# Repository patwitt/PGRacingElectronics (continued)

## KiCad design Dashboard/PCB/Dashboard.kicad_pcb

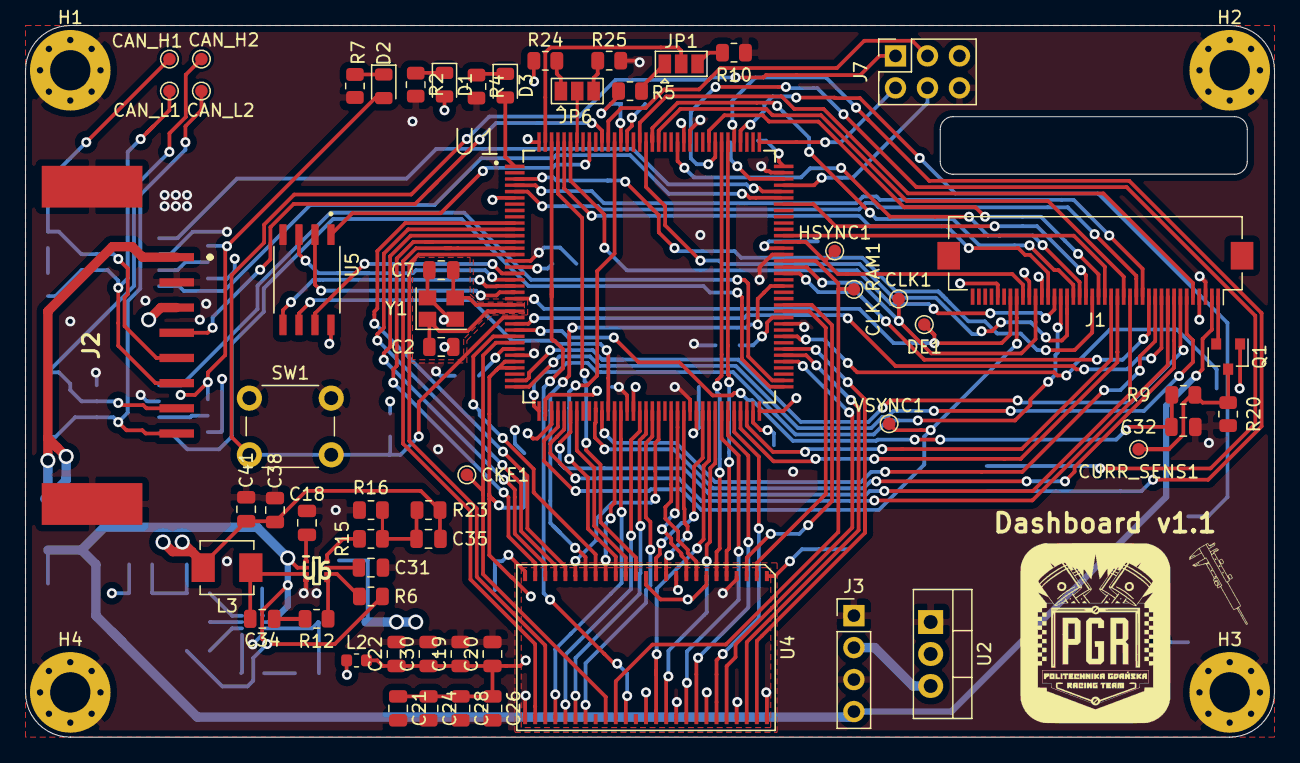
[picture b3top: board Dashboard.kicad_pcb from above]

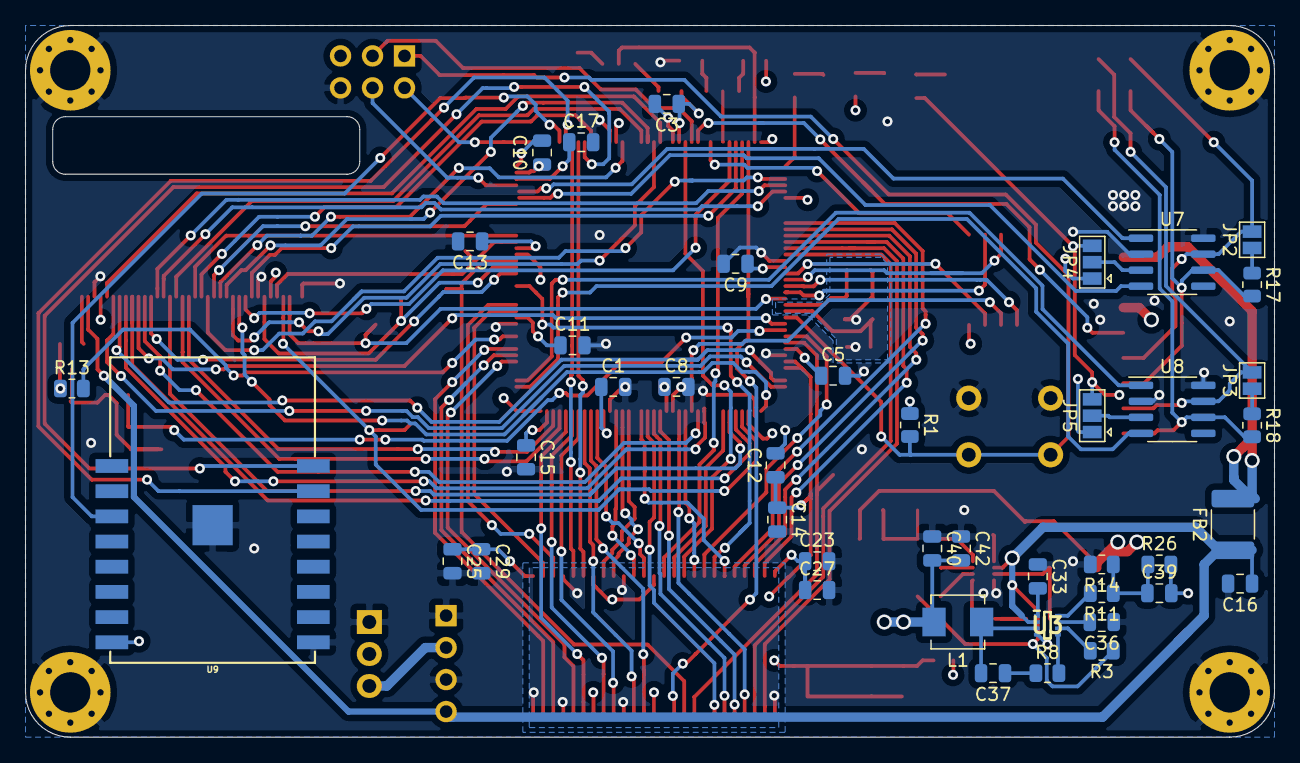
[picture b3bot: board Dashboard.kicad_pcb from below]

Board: 4 copper layers, 99.2 x 56.5 mm, 107 parts (42 on the bottom side), 131 nets.

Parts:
C1, C3, C5, C8, C9, C10, C11, C13, C16, C19, C20, C21, C22, C23, C24, C25, C26, C27, C28, C29, C30, C32: 100nF; C_0805_2012Metric
C2, C7: 14p; C_0805_2012Metric
C12, C18, C31, C33, C34, C36, C37: 1uF; C_0805_2012Metric
C14: 10nF; C_0805_2012Metric
C15, C17: 2.2uF; C_0805_2012Metric
C35, C39: 10pF; C_0805_2012Metric
C38, C40, C41, C42: 22uF; C_0805_2012Metric
CAN_H1, CAN_H2: TestPoint; TestPoint_Pad_D1.0mm
CAN_L1, CAN_L2: TestPoint; TestPoint_Pad_D1.0mm
CKE1: TestPoint; TestPoint_Pad_D1.0mm
CLK1: TestPoint; TestPoint_Pad_D1.0mm
CLK_RAM1: TestPoint; TestPoint_Pad_D1.0mm
CURR_SENS1: TestPoint; TestPoint_Pad_D1.0mm
D1: LED_3.3V; LED_0805_2012Metric
D2, D3: LED_5V; LED_0805_2012Metric
DE1: TestPoint; TestPoint_Pad_D1.0mm
FB2: Ferrite_Bead; C_1812_4532Metric
H1, H2, H3, H4: MountingHole_Pad; MountingHole_3.2mm_M3_Pad_Via
HSYNC1: TestPoint; TestPoint_Pad_D1.0mm
J1: Display; Hirose_FH12-40S-0.5SH_1x40-1MP_P0.50mm_Horizontal
J2: 34912-6080; 349126080
J3: Conn_01x04_Female; PinHeader_1x04_P2.54mm_Vertical
J7: PROGRAMMER; PinSocket_2x03_P2.54mm_Vertical
JP1: PDR_ON; SolderJumper-3_P1.3mm_Open_Pad1.0x1.5mm
JP2: CAN1_RESISTOR; SolderJumper-2_P1.3mm_Open_Pad1.0x1.5mm
JP3: CAN2_RESISTOR; SolderJumper-2_P1.3mm_Open_Pad1.0x1.5mm
JP4, JP5: Jumper_3_Bridged12; SolderJumper-3_P1.3mm_Open_Pad1.0x1.5mm
JP6: BOOT0; SolderJumper-3_P1.3mm_Open_Pad1.0x1.5mm
L1: 3.3uH; L_Vishay_IHLP-1616
L2: 39nH; L_0603_1608Metric
L3: 2.2uH; L_Vishay_IHLP-1616
Q1: Q_NMOS_GDS; SOT-23
R1, R5, R10, R24, R25: 10k; R_0805_2012Metric
R2, R4, R7, R8, R9, R12, R13: R; R_0805_2012Metric
R3, R6: 100k; R_0805_2012Metric
R11, R15: 20k; R_0805_2012Metric
R14, R16: 13k; R_0805_2012Metric
R17, R18: 120; R_0805_2012Metric
R20: 1R; R_0805_2012Metric
R23, R26: 40.2k; R_0805_2012Metric
SW1: SW_SPST; SW_PUSH_6mm_H8mm
U1: STM32F767ZIT6; QFP50P2200X2200X160-144N
U2: IFX27001TFV33; TO-220-3_Vertical
U3, U6: MP2332H; SOTFL50P160X60-8N
U4: AS4C1M16S-6TCN; TSOP-II-50
U5: AT25SF128A-SHB-T; SOIC127P790X216-8N
U7, U8: MCP2561-E-SN; SOIC-8_3.9x4.9mm_P1.27mm
U9: ESP-12S
VSYNC1: TestPoint; TestPoint_Pad_D1.0mm
Y1: Crystal_GND24; Crystal_SMD_3225-4Pin_3.2x2.5mm

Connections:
+3.3VA: C12.1, C14.1, C19.1, C20.1, C21.1, C22.1, C24.1, C26.1, C28.1, C30.1, L2.2, U1.32, U1.33, U4.7, U4.13, U4.38, U4.44
+3V3: C1.1, C3.1, C5.1, C8.1, C9.1, C10.1, C11.1, C13.1, C23.1, C25.1, C27.1, C29.1, C39.2, C40.2, C42.2, D1.2, J1.4, J1.31, JP4.1, JP5.1, L1.2, L2.1, R1.1, R5.1, R24.1, R26.2, U1.6, U1.17, U1.30, U1.39, U1.52, U1.62, U1.72, U1.84, U1.95, U1.108, U1.121, U1.131, U1.144, U2.2, U4.1, U4.25, U5.8, U9.8
+5V: C35.2, C38.2, C41.2, D2.2, J2.3, J3.2, JP4.3, JP5.3, L3.2, R23.2, U2.3
+12L: C16.1, FB2.1, J1.2, J3.4, R3.1, R6.1, U3.2, U6.2
+12V: FB2.2, J2.1
/FMC_A0: U1.10, U4.21
/FMC_A1: U1.11, U4.22
/FMC_A2: U1.12, U4.23
/FMC_A3: U1.13, U4.24
/FMC_A4: U1.14, U4.27
/FMC_A5: U1.15, U4.28
/FMC_A6: U1.50, U4.29
/FMC_A7: U1.53, U4.30
/FMC_A8: U1.54, U4.31
/FMC_A9: U1.55, U4.32
/FMC_A10: U1.56, U4.20
/FMC_BA0: U1.89, U4.19
/FMC_D0: U1.85, U4.2
/FMC_D1: U1.86, U4.3
/FMC_D2: U1.114, U4.5
/FMC_D3: U1.115, U4.6
/FMC_D4: U1.58, U4.8
/FMC_D5: U1.59, U4.9
/FMC_D6: U1.60, U4.11
/FMC_D7: U1.63, U4.12
/FMC_D8: U1.64, U4.39
/FMC_D9: U1.65, U4.40
/FMC_D10: U1.66, U4.42
/FMC_D11: U1.67, U4.43
/FMC_D12: U1.68, U4.45
/FMC_D13: U1.77, U4.46
/FMC_D14: U1.78, U4.48
/FMC_D15: U1.79, U4.49
/FMC_NBL0: U1.141, U4.14
/FMC_NBL1: U1.142, U4.36
/FMC_SDCAS: U1.132, U4.16
/FMC_SDCKE0: CKE1.1, U1.29, U4.34
/FMC_SDCLK: CLK_RAM1.1, U1.93, U4.35
/FMC_SDNE0: U1.28, U4.18
/FMC_SDNRAS: U1.49, U4.17
/FMC_SDNWE: U1.43, U4.15
/LTDC_B0: J1.21, U1.3
/LTDC_B1: J1.22, U1.102
/LTDC_B2: J1.23, U1.122
/LTDC_B3: J1.24, U1.126
/LTDC_B4: J1.25, U1.127
/LTDC_B5: J1.26, U1.37
/LTDC_B6: J1.27, U1.139
/LTDC_B7: J1.28, U1.140
/LTDC_CLK: CLK1.1, J1.30, U1.92
/LTDC_DE: DE1.1, J1.34, U1.22
/LTDC_G0: J1.13, U1.4
/LTDC_G1: J1.14, U1.5
/LTDC_G2: J1.15, U1.42
/LTDC_G3: J1.16, U1.125
/LTDC_G4: J1.17, U1.69
/LTDC_G5: J1.18, U1.70
/LTDC_G6: J1.19, U1.97
/LTDC_G7: J1.20, U1.117
/LTDC_HSYNC: HSYNC1.1, J1.32, U1.96
/LTDC_R0: J1.5, U1.128
/LTDC_R1: J1.6, U1.36
/LTDC_R2: J1.7, U1.35
/LTDC_R3: J1.8, U1.46
/LTDC_R4: J1.9, U1.41
/LTDC_R5: J1.10, U1.26
/LTDC_R6: J1.11, U1.47
/LTDC_R7: J1.12, U1.91
/LTDC_VSYNC: J1.33, U1.40, VSYNC1.1
/QUADSPI_CLK: U1.48, U5.6
/QUADSPI_IO0: U1.20, U5.5
/QUADSPI_IO1: U1.21, U5.2
/QUADSPI_IO2: U1.19, U5.3
/QUADSPI_IO3: U1.18, U5.7
/QUADSPI_NCS: U1.136, U5.1
CAN_1_1: U1.104, U7.1
CAN_1_2: U1.103, U7.4
CAN_2_1: U1.74, U8.1
CAN_2_2: U1.73, U8.4
CAN_H1: CAN_H1.1, J2.5, JP2.2, U7.7
CAN_H2: CAN_H2.1, J2.7, JP3.2, U8.7
CAN_L1: CAN_L1.1, J2.6, R17.2, U7.6
CAN_L2: CAN_L2.1, J2.8, R18.2, U8.6
DISPLAY_LED-: J1.1, Q1.2
ESP_EN: U1.112, U9.3
ESP_UART_RX: U1.113, U9.15
ESP_UART_TX: U1.116, U9.16
GND: C1.2, C2.2, C3.2, C5.2, C7.2, C8.2, C9.2, C10.2, C11.2, C12.2, C13.2, C14.2, C15.2, C16.2, C17.2, C18.1, C19.2, C20.2, C21.2, C22.2, C23.2, C24.2, C25.2, C26.2, C27.2, C28.2, C29.2, C30.2, C31.1, C32.2, C33.1, C36.1, C38.1, C40.1, C41.1, C42.1, H1.1, H2.1, H3.1, H4.1, J1.3, J1.29, J1.36, J2.2, J2.MP1, J2.MP2, J3.1, J3.3, J7.6, R2.2, R4.2, R7.2, R10.2, R14.2, R16.2, R20.2, R25.2, SW1.1, U1.16, U1.31, U1.38, U1.51, U1.61, U1.83, U1.94, U1.107, U1.120, U1.130, U2.1, U3.4, U4.4, U4.10, U4.26, U4.41, U4.47, U4.50, U5.4, U6.4, U7.2, U7.8, U8.2, U8.8, U9.9, U9.P$1, Y1.2, Y1.4
LED_CURRENT_SENSE: C32.1, R9.2, U1.27
LED_DATA: J2.4, U1.134
LED_PWM: R13.2, U1.81
unnamed: C2.1, U1.24, Y1.1
unnamed: C7.1, U1.23, Y1.3
unnamed: C18.2, U6.1
unnamed: C31.2, U6.7
unnamed: C33.2, U3.1
unnamed: C34.1, R12.1
unnamed: C34.2, L3.1, U6.3
unnamed: C35.1, R15.1, R16.1, R23.1
unnamed: C36.2, U3.7
unnamed: C37.1, R8.1
unnamed: C37.2, L1.1, U3.3
unnamed: C39.1, R11.1, R14.1, R26.1
unnamed: CURR_SENS1.1, Q1.3, R9.1, R20.1
unnamed: D1.1, R2.1
unnamed: D2.1, R7.1
unnamed: D3.1, R4.1
unnamed: JP1.1, R5.2
unnamed: JP1.2, U1.143
unnamed: JP1.3, R10.1
unnamed: JP2.1, R17.1
unnamed: JP3.1, R18.1
unnamed: JP4.2, U7.3
unnamed: JP5.2, U8.3
unnamed: JP6.1, R24.2
unnamed: JP6.2, U1.138
unnamed: JP6.3, R25.1
unnamed: Q1.1, R13.1
unnamed: R3.2, U3.6
unnamed: R6.2, U6.6
unnamed: R8.2, U3.5
unnamed: R11.2, U3.8
unnamed: R12.2, U6.5
unnamed: R15.2, U6.8
RST: J7.1, R1.2, SW1.2, U1.25
SIGNAL_LED: D3.2, U1.1
SWDCLK: J7.2, U1.109
SWDIO: J7.4, U1.105
SWIM: J7.3, U1.133
VCAP1: C15.1, U1.71
VCAP2: C17.1, U1.106

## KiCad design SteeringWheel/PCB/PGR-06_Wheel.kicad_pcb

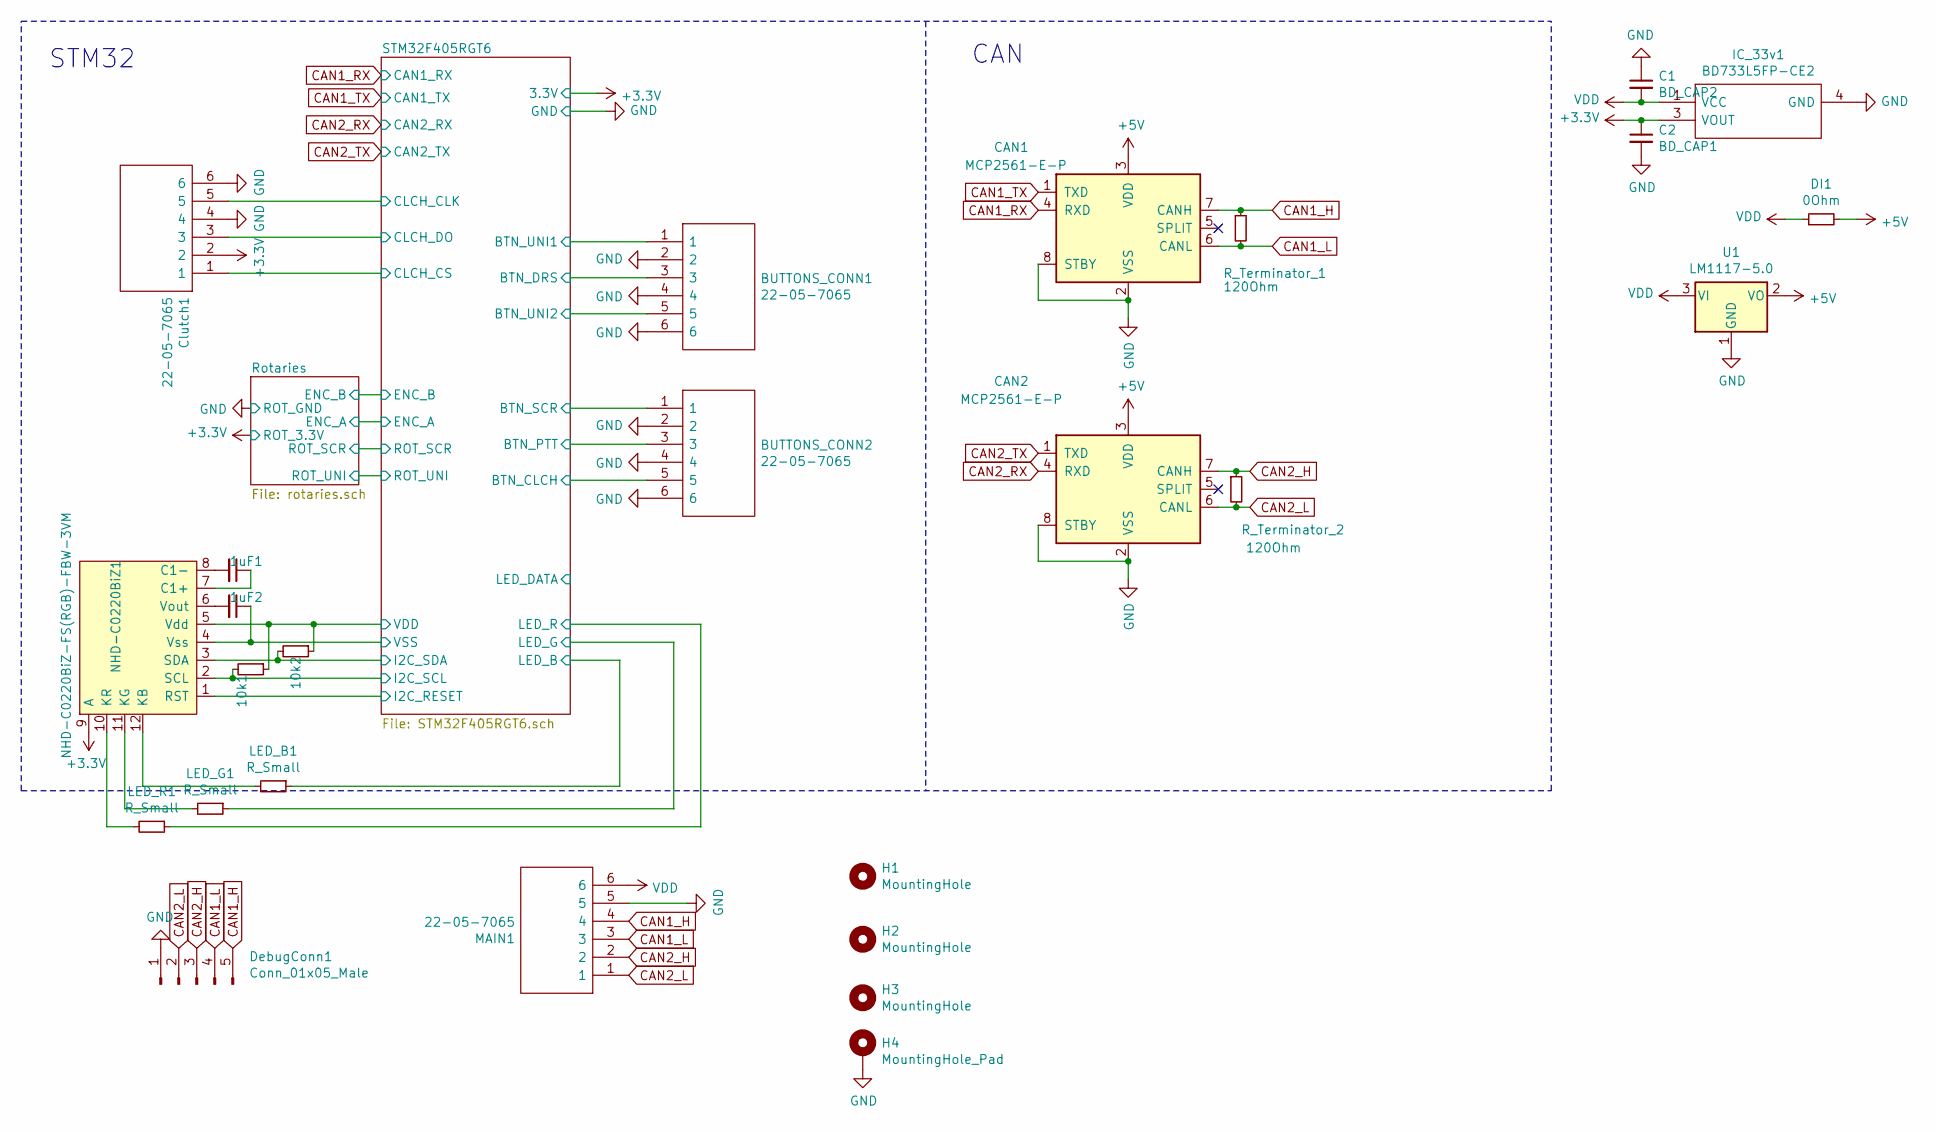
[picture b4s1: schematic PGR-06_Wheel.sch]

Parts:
1uF1, 1uF2: C_Small; C_0603_1608Metric
10k1, 10k2: R_Small; R_0805_2012Metric
BUTTONS_CONN1, BUTTONS_CONN2: 22-05-7065; 22057065; Manufacturer_Part_Number 22-05-7065; Mouser Part Number 538-22-05-7065
C1: BD_CAP2; C_0805_2012Metric
C2: BD_CAP1; C_0805_2012Metric
CAN1, CAN2: MCP2561-E-P; DIP-8_W7.62mm
Clutch1: 22-05-7065; 22057065; Manufacturer_Part_Number 22-05-7065; Mouser Part Number 538-22-05-7065
DI1: 0Ohm; R_0805_2012Metric
DebugConn1: Conn_01x05_Male; PinHeader_1x05_P2.54mm_Vertical
H1, H2, H3: MountingHole; MountingHole_3.2mm_M3
H4: MountingHole_Pad; MountingHole_3.2mm_M3_Pad_TopBottom
IC_33v1: BD733L5FP-CE2; BD750L5FPCE2; Manufacturer_Part_Number BD733L5FP-CE2; Mouser Part Number 755-BD733L5FP-CE2
LED_B1: R_Small; R_0805_2012Metric
LED_G1: R_Small; R_0805_2012Metric
LED_R1: R_Small; R_0805_2012Metric
MAIN1: 22-05-7065; 22057065; Manufacturer_Part_Number 22-05-7065; Mouser Part Number 538-22-05-7065
NHD-C0220BiZ1: NHD-C0220BiZ-FS(RGB)-FBW-3VM; NHD-C0220BiZ-FS(RGB)-FBW-3VM-NEW
R_Terminator_1, R_Terminator_2: 120Ohm; R_0805_2012Metric
U1: LM1117-5.0; TO-252-2

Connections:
+3V3: 10k1.1, 10k2.1, C2.1, Clutch1.2, IC_33v1.3 (VOUT), NHD-C0220BiZ1.5 (Vdd), NHD-C0220BiZ1.9 (A); also elsewhere on the board
+5V: CAN1.3 (VDD), CAN2.3 (VDD), DI1.2, U1.2 (VO)
/STM32F405RGT6/BTN_CLCH: BUTTONS_CONN2.5; also elsewhere on the board
/STM32F405RGT6/BTN_DRS: BUTTONS_CONN1.3; also elsewhere on the board
/STM32F405RGT6/BTN_PTT: BUTTONS_CONN2.3; also elsewhere on the board
/STM32F405RGT6/BTN_SCR: BUTTONS_CONN2.1; also elsewhere on the board
/STM32F405RGT6/BTN_UNI1: BUTTONS_CONN1.1; also elsewhere on the board
/STM32F405RGT6/BTN_UNI2: BUTTONS_CONN1.5; also elsewhere on the board
/STM32F405RGT6/CLCH_CLK: Clutch1.5; also elsewhere on the board
/STM32F405RGT6/CLCH_CS: Clutch1.1; also elsewhere on the board
/STM32F405RGT6/CLCH_DO: Clutch1.3; also elsewhere on the board
/STM32F405RGT6/I2C_RESET: NHD-C0220BiZ1.1 (RST); also elsewhere on the board
/STM32F405RGT6/I2C_SCL: 10k1.2, NHD-C0220BiZ1.2 (SCL); also elsewhere on the board
/STM32F405RGT6/I2C_SDA: 10k2.2, NHD-C0220BiZ1.3 (SDA); also elsewhere on the board
/STM32F405RGT6/LED_B: LED_B1.1; also elsewhere on the board
/STM32F405RGT6/LED_G: LED_G1.1; also elsewhere on the board
/STM32F405RGT6/LED_R: LED_R1.1; also elsewhere on the board
CAN1_H: CAN1.7 (CANH), DebugConn1.5, MAIN1.4, R_Terminator_1.1
CAN1_L: CAN1.6 (CANL), DebugConn1.4, MAIN1.3, R_Terminator_1.2
CAN1_RX: CAN1.4 (RXD); also elsewhere on the board
CAN1_TX: CAN1.1 (TXD); also elsewhere on the board
CAN2_H: CAN2.7 (CANH), DebugConn1.3, MAIN1.2, R_Terminator_2.1
CAN2_L: CAN2.6 (CANL), DebugConn1.2, MAIN1.1, R_Terminator_2.2
CAN2_RX: CAN2.4 (RXD); also elsewhere on the board
CAN2_TX: CAN2.1 (TXD); also elsewhere on the board
GND: 1uF2.1, BUTTONS_CONN1.2, BUTTONS_CONN1.4, BUTTONS_CONN1.6, BUTTONS_CONN2.2, BUTTONS_CONN2.4, BUTTONS_CONN2.6, C1.1, C2.2, CAN1.2 (VSS), CAN1.8 (STBY), CAN2.2 (VSS), CAN2.8 (STBY), Clutch1.4, Clutch1.6, DebugConn1.1, H4.1, IC_33v1.4 (GND), MAIN1.5, NHD-C0220BiZ1.4 (Vss), U1.1 (GND); also elsewhere on the board
unnamed: 1uF1.1, NHD-C0220BiZ1.7 (C1+)
unnamed: 1uF1.2, NHD-C0220BiZ1.8 (C1-)
unnamed: 1uF2.2, NHD-C0220BiZ1.6 (Vout)
unnamed: LED_B1.2, NHD-C0220BiZ1.12 (KB)
unnamed: LED_G1.2, NHD-C0220BiZ1.11 (KG)
unnamed: LED_R1.2, NHD-C0220BiZ1.10 (KR)
VDD: C1.2, DI1.1, IC_33v1.1 (VCC), MAIN1.6, U1.3 (VI)

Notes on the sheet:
CAN
STM32

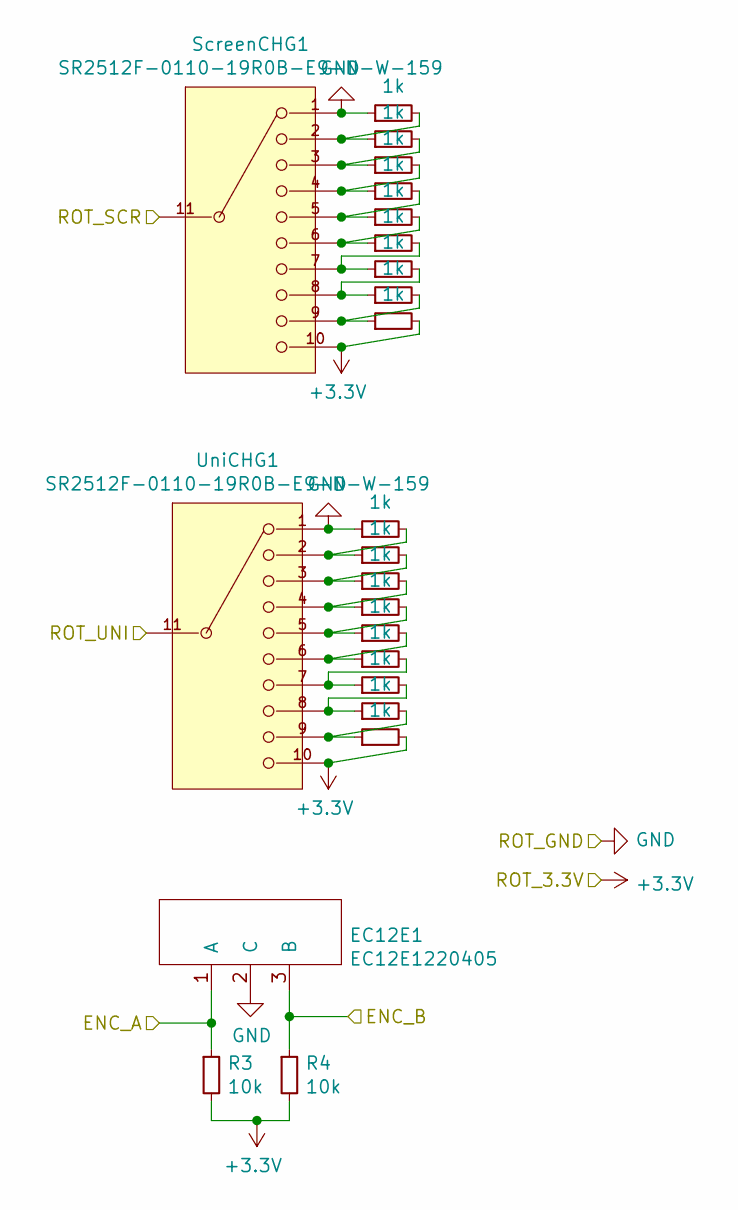
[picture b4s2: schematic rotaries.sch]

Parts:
1k1, 1k2, 1k3, 1k4, 1k5, 1k6, 1k7, 1k8, 1k9, 1k10, 1k11, 1k12, 1k13, 1k14, 1k15, 1k16, 1k17, 1k18: 1k; R_0805_2012Metric
EC12E1: EC12E1220405
R3, R4: 10k; R_0805_2012Metric
ScreenCHG1: SR2512F-0110-19R0B-E9-N-W-159; Alpha_Taiwan-SR2512F-0110-19R0B-E9-N-W-159-MFG; voltage rating AC 125V; mouser part number 105-SR2512F-110NS
UniCHG1: SR2512F-0110-19R0B-E9-N-W-159; Alpha_Taiwan-SR2512F-0110-19R0B-E9-N-W-159-MFG; voltage rating AC 125V; mouser part number 105-SR2512F-110NS

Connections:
+3V3: 1k9.2, 1k18.2, R3.2, R4.2, ScreenCHG1.10, UniCHG1.10; also elsewhere on the board
/Rotaries/ENC_A: EC12E1.1 (A), R3.1; also elsewhere on the board
/Rotaries/ENC_B: EC12E1.3 (B), R4.1; also elsewhere on the board
/Rotaries/ROT_SCR: ScreenCHG1.11 (Pole); also elsewhere on the board
/Rotaries/ROT_UNI: UniCHG1.11 (Pole); also elsewhere on the board
GND: 1k1.1, 1k10.1, EC12E1.2 (C), ScreenCHG1.1, UniCHG1.1; also elsewhere on the board
unnamed: 1k1.2, 1k2.1, UniCHG1.2
unnamed: 1k2.2, 1k3.1, UniCHG1.3
unnamed: 1k3.2, 1k4.1, UniCHG1.4
unnamed: 1k4.2, 1k5.1, UniCHG1.5
unnamed: 1k5.2, 1k6.1, UniCHG1.6
unnamed: 1k6.2, 1k7.1, UniCHG1.7
unnamed: 1k7.2, 1k8.1, UniCHG1.8
unnamed: 1k8.2, 1k9.1, UniCHG1.9
unnamed: 1k10.2, 1k11.1, ScreenCHG1.2
unnamed: 1k11.2, 1k12.1, ScreenCHG1.3
unnamed: 1k12.2, 1k13.1, ScreenCHG1.4
unnamed: 1k13.2, 1k14.1, ScreenCHG1.5
unnamed: 1k14.2, 1k15.1, ScreenCHG1.6
unnamed: 1k15.2, 1k16.1, ScreenCHG1.7
unnamed: 1k16.2, 1k17.1, ScreenCHG1.8
unnamed: 1k17.2, 1k18.1, ScreenCHG1.9

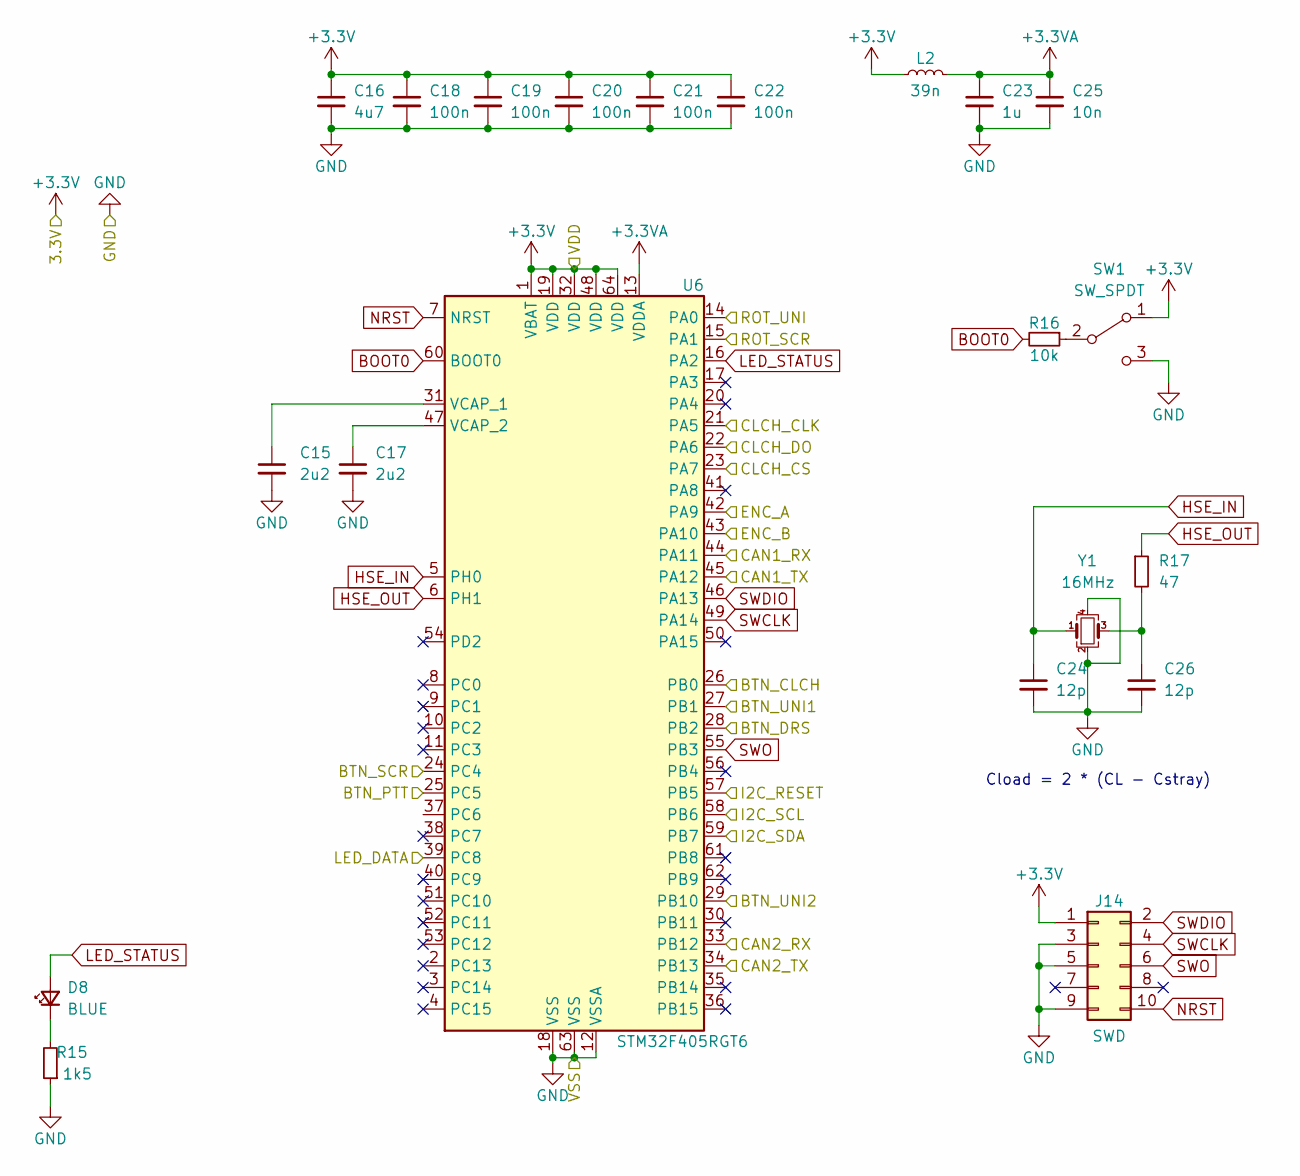
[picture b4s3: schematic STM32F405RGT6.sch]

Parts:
C15, C17: 2u2; C_0805_2012Metric; LCSC Part # C23630
C16: 4u7; C_0805_2012Metric; LCSC Part # C19666
C18, C19, C20, C21, C22: 100n; C_0805_2012Metric; LCSC Part # C1525
C23: 1u; C_0805_2012Metric; LCSC Part # C52923
C24, C26: 12p; C_0805_2012Metric; LCSC Part # C1547
C25: 10n; C_0805_2012Metric; LCSC Part # C15195
D8: BLUE; LED_0603_1608Metric; LCSC Part # C72041
J14: SWD; PinHeader_2x05_P1.27mm_Vertical_SMD
L2: 39n; L_0402_1005Metric; LCSC Part # C26443
R15: 1k5; R_0805_2012Metric; LCSC Part # C22843
R16: 10k; R_0805_2012Metric; LCSC Part # C25744
R17: 47; R_0805_2012Metric; LCSC Part # C25118
SW1: SW_SPDT; SW_SPDT_PCM12
U6: STM32F405RGT6; LQFP-64_10x10mm_P0.5mm; LCSC Part # C15742
Y1: 16MHz; OSCCC500X320X110-4N; LCSC Part # C13738

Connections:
+3.3VA: C23.1, C25.1, L2.2, U6.13 (VDDA)
+3V3: C16.1, C18.1, C19.1, C20.1, C21.1, C22.1, J14.1, L2.1, SW1.1 (A), U6.1 (VBAT), U6.19 (VDD), U6.32 (VDD), U6.48 (VDD), U6.64 (VDD); also elsewhere on the board
/Rotaries/ENC_A: U6.42 (PA9); also elsewhere on the board
/Rotaries/ENC_B: U6.43 (PA10); also elsewhere on the board
/Rotaries/ROT_SCR: U6.41 (PA8); also elsewhere on the board
/Rotaries/ROT_UNI: U6.40 (PC9); also elsewhere on the board
/STM32F405RGT6/BTN_CLCH: U6.26 (PB0); also elsewhere on the board
/STM32F405RGT6/BTN_DRS: U6.28 (PB2); also elsewhere on the board
/STM32F405RGT6/BTN_PTT: U6.25 (PC5); also elsewhere on the board
/STM32F405RGT6/BTN_SCR: U6.24 (PC4); also elsewhere on the board
/STM32F405RGT6/BTN_UNI1: U6.27 (PB1); also elsewhere on the board
/STM32F405RGT6/BTN_UNI2: U6.29 (PB10); also elsewhere on the board
/STM32F405RGT6/CLCH_CLK: U6.21 (PA5); also elsewhere on the board
/STM32F405RGT6/CLCH_CS: U6.23 (PA7); also elsewhere on the board
/STM32F405RGT6/CLCH_DO: U6.22 (PA6); also elsewhere on the board
/STM32F405RGT6/I2C_RESET: U6.57 (PB5); also elsewhere on the board
/STM32F405RGT6/I2C_SCL: U6.58 (PB6); also elsewhere on the board
/STM32F405RGT6/I2C_SDA: U6.59 (PB7); also elsewhere on the board
/STM32F405RGT6/LED_B: U6.35 (PB14); also elsewhere on the board
/STM32F405RGT6/LED_G: U6.36 (PB15); also elsewhere on the board
/STM32F405RGT6/LED_R: U6.37 (PC6); also elsewhere on the board
BOOT0: R16.2, U6.60 (BOOT0)
CAN1_RX: U6.44 (PA11); also elsewhere on the board
CAN1_TX: U6.45 (PA12); also elsewhere on the board
CAN2_RX: U6.33 (PB12); also elsewhere on the board
CAN2_TX: U6.34 (PB13); also elsewhere on the board
GND: C15.2, C16.2, C17.2, C18.2, C19.2, C20.2, C21.2, C22.2, C23.2, C24.2, C25.2, C26.2, J14.3, J14.5, J14.9, R15.1, SW1.3 (C), U6.12 (VSSA), U6.18 (VSS), U6.63 (VSS), Y1.2, Y1.4; also elsewhere on the board
HSE_IN: C24.1, U6.5 (PH0), Y1.1
HSE_OUT: R17.1, U6.6 (PH1)
LED_STATUS: D8.2 (A), U6.16 (PA2)
NRST: J14.10, U6.7 (NRST)
unnamed: C15.1, U6.31 (VCAP_1)
unnamed: C17.1, U6.47 (VCAP_2)
unnamed: C26.1, R17.2, Y1.3
unnamed: D8.1 (K), R15.2
unnamed: R16.1, SW1.2 (B)
SWCLK: J14.4, U6.49 (PA14)
SWDIO: J14.2, U6.46 (PA13)
SWO: J14.6, U6.55 (PB3)

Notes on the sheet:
Cload = 2 * (CL - Cstray)

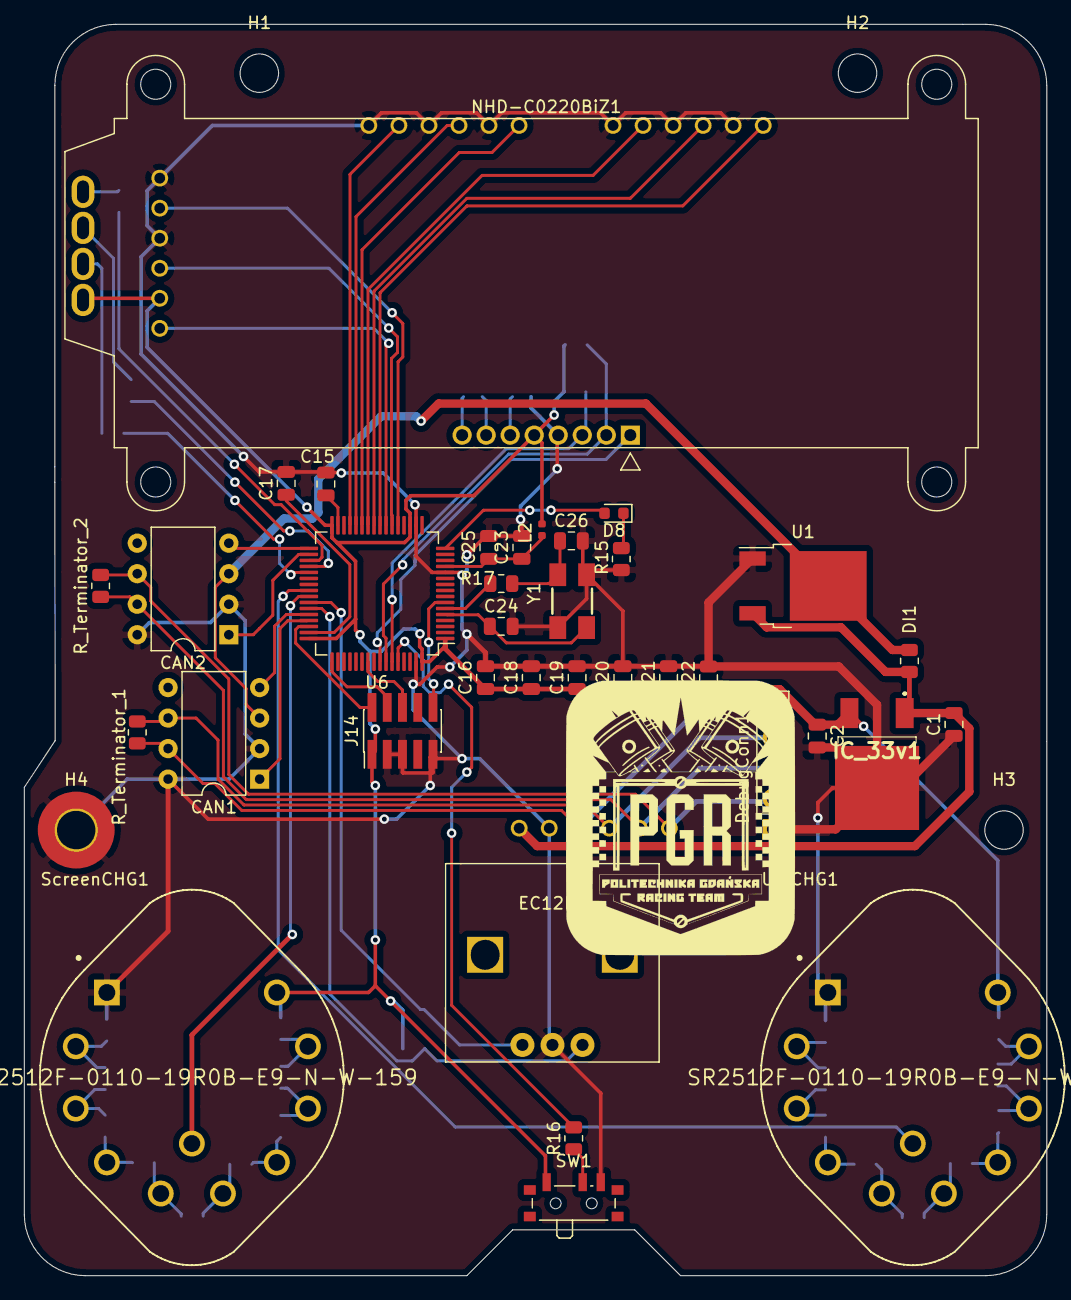
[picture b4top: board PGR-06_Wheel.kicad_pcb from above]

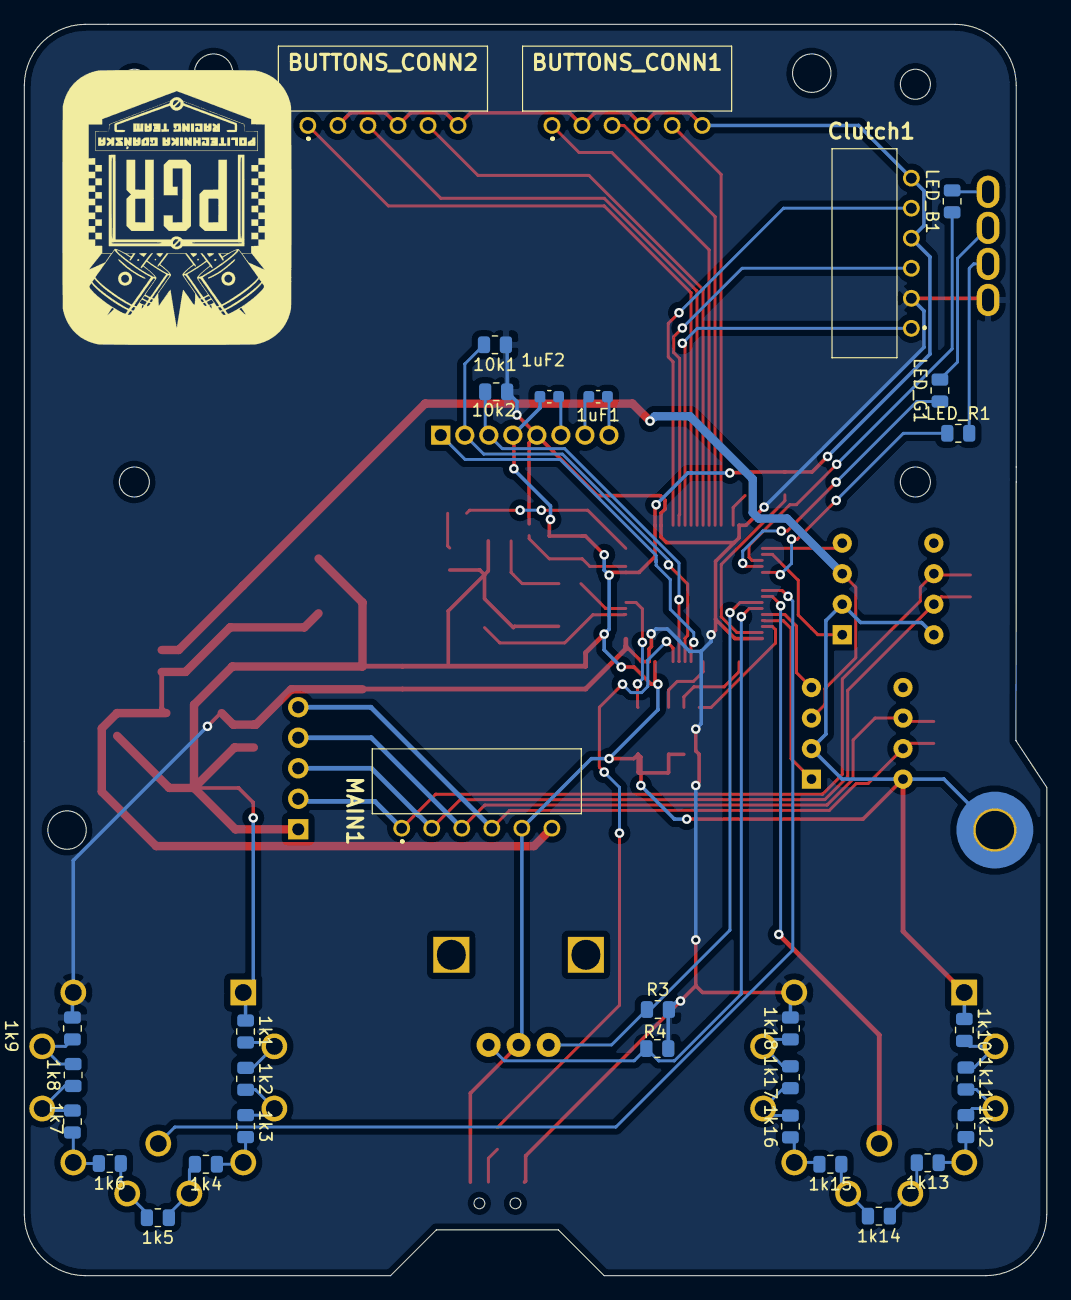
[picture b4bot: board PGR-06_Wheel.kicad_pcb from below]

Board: 2 copper layers, 85.1 x 104.1 mm, 70 parts (31 on the bottom side), 67 nets.

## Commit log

2021-11-01 Initial commit for GearControl and PDM PCB's
2021-11-01 Initial ReadMe
2021-11-01 Initial empty project for Gear Control v2 on STM32F4
2021-11-03 Initial commit Dash PGR-05
2021-11-03 Initial commit Telemetry - added telem.py code for interpreting pixhawk specific data
2021-11-03 Added PGR05 Dash code - not sure if newest
2021-11-04 New radnom file
2021-11-11 Added main.c file
2021-11-14 Add KiCAD common libraries
2021-11-15 New Steering wheel scheme
2021-11-17 Add buck converter
2021-11-22 Add Steering wheel model for PGR-06
2021-11-29 update kicad libs
2021-12-29 Steering Wheel Update
2021-12-29 Steering Wheel Update (#5)
2021-12-29 Remove unnecessary files
2021-12-30 Dashboard merge
    * Initial commit
    * Add buck converter
    * Remove unnecessary files
2022-01-09 initial commit telemtry schematic
2022-01-09 initial commit telemtry schematic (#7)
2022-01-09 Update PDM PCB
2022-01-16 rm files
2022-01-18 Dashboard (#9)
2022-01-18 Add correct files
2022-02-19 Add project config
2022-02-20 Added new brd for steering wheel
2022-02-22 New brd for steering wheel
2022-02-22 AT25SF128A External Loader for STM32CubeProgrammer
2022-02-22 At25 sf128 a external loader (#13)
    * AT25SF128A External Loader for STM32CubeProgrammer
2022-02-22 New brd for steering wheel (#12)
2022-02-22 Initial config for Display
2022-02-22 ADD new pcb files
2022-02-22 working display
2022-02-23 New pcb board
2022-02-23 Add signal led
2022-03-01 Some stuff
2022-03-01 Flash config
2022-03-01 Fix write error
2022-03-01 Dashboard (#15)
    * Initial commit
    * Add buck converter
    * Remove unnecessary files
    * rm files
    * Add correct files
    * Add project config
2022-03-01 Required 3D models for steering wheel
2022-03-01 Display and CubeIde config for SteeringWheel
2022-03-01 SOIC12 footprint
2022-03-01 Symbols for SW
2022-03-01 Add gitignore
2022-03-01 Steering wheel3 (#17)
    * New brd for steering wheel
    * Required 3D models for steering wheel
    * Display and CubeIde config for SteeringWheel
    * SOIC12 footprint
    * Symbols for SW
2022-03-01 Add gitignore (#16)
2022-03-01 Add makefile for internal and external flash
2022-03-01 Add usb C to board
2022-03-03 Add reset and pd pin to esp
2022-03-03 Switch footprints of converter
2022-03-03 Add pins for esp
2022-03-14 telemetry code init
2022-03-14 telemetry code init (#19)
2022-03-16 Add LED Driver
2022-03-17 Add text to pcb
2022-03-20 init commit
2022-03-21 Telemetry PCB added
2022-03-31 mlx90640 init
2022-03-31 PCB v1.0 (#21)
    * Add usb C to board
    * Add reset and pd pin to esp
    * Switch footprints of converter
    * Add LED Driver
    * Add text to pcb
2022-03-31 New brd design & final scheme
2022-03-31 final scheme & 60%pcb
2022-04-05 almost finished - space for Bartek
2022-04-07 Telemetry back (#24)
    * init commit
    * New brd design & final scheme
    * final scheme & 60%pcb
    * almost finished - space for Bartek
2022-04-07 mlx90640
2022-04-07 dzialaj prosze
2022-04-07 dzialaj prosze (#25)
2022-04-27 pre_finnal
2022-04-29 telemetry_back_finnal
2022-04-30 kicad libs
2022-05-04 finnal
2022-05-05 Remove Dashboard files from this branch
    This reverts commit ffcd00ee911598f18239aabaf1713ea3aea0f91a.
2022-05-05 Telemetry back v1.0 (#27)
    * init commit
    * New brd design & final scheme
    * final scheme & 60%pcb
    * almost finished - space for Bartek
    * pre_finnal
    * pre_finnal
2022-05-09 Remove PDM files
2022-05-09 Telemetry PCB added (#22)
    * Telemetry PCB added
    * Remove PDM files
2022-05-10 Add code for GearControl V1 (2021 working)
2022-05-10 Add PCB for PDM
2022-05-10 Add PCB for GearControl V1 (2021)
2022-05-10 Add missing files for GearControl V1
2022-05-15 Set settings for external flash and ram
2022-05-15 Increse flash clock
2022-05-25 Read data from ecumaster can to struct
2022-05-26 started code for telemtry saving
2022-05-26 add some files
2022-05-29 BSPD_PCB
2022-05-30 BSPD_PCB (#28)
2022-06-02 Telemetry_back v1.1
2022-06-02 almost done pcb (check communication with adc)
    almost done pcb (check communication with adc)
2022-06-04 BSPD
    With Gerbers
2022-06-13 Added MLX
2022-06-13 added missing files
2022-06-13 removed tracking files
2022-06-15 Fix ltdc and ram
2022-06-16 update gearcontrol v2
2022-06-18 latest updates for DBW controller and PID
2022-06-18 Add stm32f767 datasheets
2022-06-19 latest gear control updates
2022-06-20 Telemetry_back_v1.1
2022-06-20 Telemetry_back v1.1 (#31)
    * Telemetry_back v1.1
    * Telemetry_back_v1.1
    * Telemetry_back_v1.1
2022-06-27 Some code added
2022-06-27 added vss config + callback
2022-06-27 some name refactoring
2022-06-27 add old PDM
2022-06-29 GearControl v3 PCB
2022-07-07 even more code
2022-07-08 latest Gearcontrol V2 code
2022-07-08 remove old files
2022-07-08 update macro config
2022-07-08 remove .setting local
2022-07-11 Add Clutch Control from CAN. IMPORTANT - CHANGE CONFIG_ENABLE_CAN to TRUE after CAN is setup correctly in CubeMX!
2022-07-11 small servo update
2022-07-12 gear control updates
2022-07-24 New PCB for Dashboard
2022-07-26 some shit
2022-07-28 Some amazing features
2022-08-01 New updates on Gear Control
2022-08-01 fix servo range
2022-08-03 Steering Wheel update --working display + clutch paddle + can
2022-08-04 Fix gear state
2022-08-04 update gear states mapping
2022-08-04 fix request check
2022-08-04 update switch for requests
2022-08-05 update project config
2022-08-07 Test Setup
2022-08-07 Add stm32f767 datasheets (#30)
2022-08-07 Working display with can
    * Add makefile for internal and external flash
    * Add pins for esp
    * Set settings for external flash and ram
    * Increse flash clock
    * Read data from ecumaster can to struct
    * Fix ltdc and ram
2022-08-07 Gear control updates, clutch operations and injectors
2022-08-07 update Gear Control + add doxy
2022-08-07 Add new PCB for Dashboard (#34)
    * Add usb C to board
    * Add reset and pd pin to esp
    * Switch footprints of converter
    * Add LED Driver
    * Add text to pcb
    * New PCB for Dashboard
2022-08-07 update doxys
2022-08-07 update gear sensor adc
2022-08-07 small fixes
2022-08-08 fix PWM
2022-08-08 Telemetry_back_v2
2022-08-10 Gear control updates, add rev matching
2022-08-10 small updates
2022-08-11 Led and freertos code refactor
2022-08-12 update CAN
2022-08-13 Added Can + sending Ecumaster structure by rfd module
2022-08-15 GPS ang GYRO active, sending ecu data
2022-08-15 Gear requests fix and refactor, CAN config update
2022-08-16 Set oil, gear unkonwn alert
2022-08-16 fsg start
    can config modification
2022-08-18 Refactor led code
2022-08-19 Fix minor bugs
2022-08-24 Steering wheel status, calc fuel usage
2022-08-24 Changed ecu freq, added new can frame
2022-08-25 can id fix
    can msg id resloved by enum, default pwm changed
2022-08-26 gear control fixes
2022-08-26 reduce gear sens monitoring time. update init range condition
2022-08-27 alpe adria fixes
2022-08-27 add comments
2022-08-27 add injectors cut
2022-08-27 add timing stats to CAN msg
2022-08-28 Gear control fsg (#36)
    * fsg start
    can config modification
    * can id fix
    can msg id resloved by enum, default pwm changed
    * alpe adria fixes
    * updates
2022-08-28 refactor gear control
2022-09-13 Add more files do gitignore
2022-09-13 New project version
2022-09-13 Fix compile errors
2022-09-19 Telemetry_back
2022-09-25 Initial scheme
2022-09-25 Final schematic
2022-09-25 Minor changes, attached footprints
2022-09-28 update gitignore
2022-09-28 Setup adc with timer
2022-10-01 Add CAN communication initialization
2022-10-01 Telemetry (#35)
    * Telemetry_back v1.1
    * Telemetry_back_v1.1
    * Telemetry_back_v1.1
    * Telemetry_back_v2
    * Telemetry_back
2022-10-02 Setup freertos function for led bar
2022-10-05 .remove libraries and execs from gitignore
2022-10-05 Adc on timer, add Middleware files
2022-10-10 with vss and damper
2022-10-13 Code cleanup
2022-11-03 Fixed GPS, changed adc to use dma, change abs calcualtions
2022-11-03 Minor code refacoring
2022-11-04 STABLE fot tests 04.11
2022-11-04 NOT TESTED added sending data to module and sending can frames
2022-11-04 Quick Fix
2022-11-09 Version 09.11
    ABS new calculation, raw data CAN sending
2022-11-10 Changed abs calculation method
2023-05-20 DBW updates
2023-06-13 Latest updates for smaller Bosch Throttle Body
2023-07-08 Added safety system for DBW
2023-11-03 Version 1.0.0, active: GPS, IMU, 4xDamper, Steering Wheel, 2xABS
2024-02-04 Update GearCtrl PCB for safety system for ETB
2024-02-15 Added gitignore
2024-02-15 Test1
2024-03-21 Update code
2024-03-23 initial testing of new ETB
2024-05-27 add kalman, fix PID
2024-06-28 FIXES FOR NEW PCB!
2024-07-09 Flashed code
2024-07-10 Rules compliant DBW
2024-07-10 Update feasible range
2024-07-15 DBW refactor + rules fixes
2024-07-18 Further updates, Throttle Blip updates
2024-07-18 Reset safaty only on idle tps
2024-08-01 Update Pid params
2024-08-01 Update apps range, add gamma
2024-08-03 throttle blip
2024-08-03 Fixes for safety after refactor
2024-08-04 Add Marcin Throttle Blip
2025-05-04 gc as adc to can
